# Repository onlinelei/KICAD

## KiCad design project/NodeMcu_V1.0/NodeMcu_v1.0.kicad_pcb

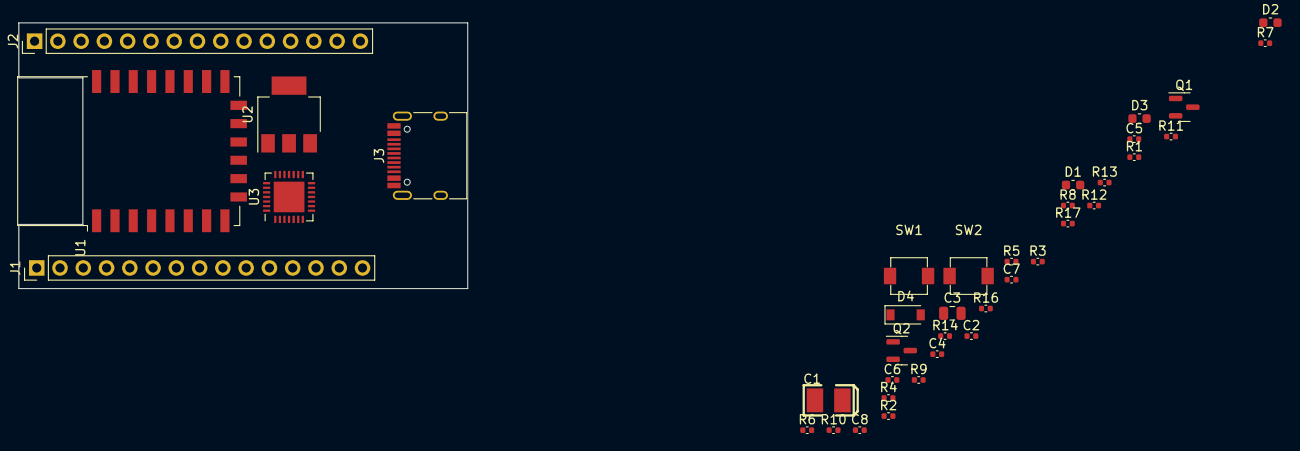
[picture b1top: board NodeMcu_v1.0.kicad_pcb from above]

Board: 2 copper layers, 49.0 x 29.0 mm, 38 parts (0 on the bottom side), 37 nets, no tracks yet.

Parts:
C1: 100uf; CASE-B_3528
C2, C6, C7: 100nf; C_0402_1005Metric
C3: 10uf 25v; C_0805_2012Metric
C4, C5, C8: 10uf; C_0402_1005Metric
D1: 3.3; C_0603_1608Metric
D2: TXD; C_0603_1608Metric
D3: RXD; C_0603_1608Metric
D4: B120-E3; D_SOD-123
J1: J2; PinHeader_1x15_P2.54mm_Vertical
J2: J1; PinHeader_1x15_P2.54mm_Vertical
J3: usbc; USB_C_Receptacle_HRO_TYPE-C-31-M-12
Q1: q1; SOT-23
Q2: q2; SOT-23
R1, R3, R10, R11, R12, R14: 12K; C_0402_1005Metric
R2, R8, R9, R13: 470; C_0402_1005Metric
R4, R5: 1k; C_0402_1005Metric
R6: 12k; C_0402_1005Metric
R7: 0; C_0402_1005Metric
R16: 220K(1%); C_0402_1005Metric
R17: 100K(1%); C_0402_1005Metric
SW1, SW2: SW_Push; SMD,3x4x2mm
U1: ESP-12E
U2: NCP1117-1.5_SOT223; SOT-223
U3: CP2102-GMR_[C6568]; QFN-28-1EP_5x5mm_P0.5mm_EP3.35x3.35mm

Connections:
+3V3: C1.1, C4.1, C5.1, C6.1, J1.11, J2.6, J2.15, R1.2, R2.1, R3.2, R4.1, R5.1, R6.2, R10.2, U1.8 (VCC), U2.2 (VO), U3.6 (VDD), U3.7 (REGIN)
+5VD: C3.1, D4.1 (K), U2.3 (VI)
/ADC: J1.2, R16.1, R17.1, U1.2 (ADC)
/ADC EX: J1.1, R16.2
/EN: J1.12, R6.1, U1.3 (EN)
/GPIO0: J2.4, Q2.3 (C), R1.1, R9.1, U1.18 (GPIO0)
/GPIO2: J2.5, R3.1, U1.17 (GPIO2)
/GPIO4: J2.3, U1.19 (GPIO4)
/GPIO5: J2.2, U1.20 (GPIO5)
/GPIO9: J1.5, U1.11 (GPIO9)
/GPIO10: J1.4, U1.12 (GPIO10)
/GPIO12: J2.9, U1.6 (GPIO12)
/GPIO13: J2.10, U1.7 (GPIO13)
/GPIO14: J2.8, U1.5 (GPIO14)
/GPIO15: J2.11, R11.1, U1.16 (GPIO15)
/GPIO16: D1.1 (K), J2.1, R7.1, U1.4 (GPIO16)
/RXD: D3.1 (K), J2.12, R13.1, U1.21 (GPIO3/RXD)
/SPI_CLK: J1.9, U1.14 (SCLK)
/SPI_INT: J1.6, U1.13 (MOSI)
/SPI_MISO: J1.8, U1.10 (MISO)
/SPI_MOSI: J1.7, U1.9 (CS0)
/TXD: D2.1 (K), J2.13, U1.22 (GPIO1/TXD), U3.25 (RXD)
/VDDUSB: C7.1, C8.1, D4.2 (A), J1.15, J3.A4 (VBUS), J3.A9 (VBUS), J3.B4 (VBUS), J3.B9 (VBUS), U3.8 (VBUS)
/nRST: C2.2, J1.13, Q1.3 (C), R8.1, R10.1, U1.1 (~RST)
GND: C1.2, C2.1, C3.2, C4.2, C5.2, C6.2, C7.2, C8.2, J1.10, J1.14, J2.7, J2.14, J3.A1 (GND), J3.A12 (GND), J3.B1 (GND), J3.B12 (GND), J3.S1 (SHIELD), R11.2, R17.2, SW1.2, SW2.2, U1.15 (GND), U2.1 (GND), U3.3 (GND)
unnamed: D1.2 (A), R2.2
unnamed: D2.2 (A), R4.2
unnamed: D3.2 (A), R5.2
unnamed: J3.A6 (D+), J3.B6 (D+), U3.4 (D+)
unnamed: J3.A7 (D-), J3.B7 (D-), U3.5 (D-)
unnamed: Q1.1 (B), R12.1
unnamed: Q1.2 (E), R14.2, U3.24 (RTS)
unnamed: Q2.1 (B), R14.1
unnamed: Q2.2 (E), R12.2, U3.28 (DTR)
unnamed: R7.2, R8.2, SW1.1
unnamed: R9.2, SW2.1
unnamed: R13.2, U3.26 (TXD)

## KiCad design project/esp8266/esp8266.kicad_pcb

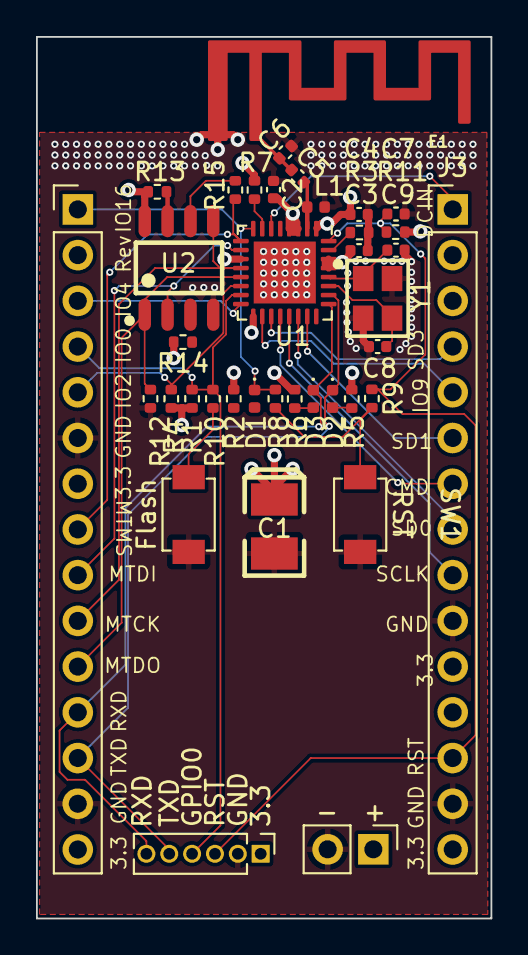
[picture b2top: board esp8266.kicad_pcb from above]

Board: 4 copper layers, 25.2 x 49.0 mm, 38 parts (0 on the bottom side), 34 nets.

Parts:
C1: 100uf; CASE-B_3528
C2: 1uF; C_0402_1005Metric
C3: 10uF; C_0402_1005Metric
C4: 0.1uF; C_0402_1005Metric
C5: 8.2pF; C_0402_1005Metric
C6: 2.4pF; C_0402_1005Metric
C7: 470pf; C_0402_1005Metric
C8, C9: 10pF; C_0402_1005Metric
D1: 3.3; LED_0402_1005Metric
D2: TXD; LED_0402_1005Metric
D3: RXD; LED_0402_1005Metric
E1: ANTENNA-GROUNDEDTRACE-15.2MM; RF_2.4GHZ_15.2MM
J1: power; PinHeader_1x02_P2.54mm_Vertical
J2: TTL; PinHeader_1x06_P1.27mm_Vertical
J3, J4: Conn_01x15_Female; PinHeader_1x15_P2.54mm_Vertical
L1: 1.5nH; L_0402_1005Metric
R1, R3, R4, R11, R12: 12K; R_0402_1005Metric
R2, R9, R10: 470; R_0402_1005Metric
R5, R6: 1k; R_0402_1005Metric
R7: 12k; R_0402_1005Metric
R8: 0; R_0402_1005Metric
R13, R14: 10K; R_0402_1005Metric
R15: 50; R_0402_1005Metric
SW1: RST; Button_SMD,3x4x2mm
SW2: Flash; Button_SMD,3x4x2mm
U1: ESP8266EX; QFN-32-1EP_5x5mm_P0.5mm_EP3.45x3.45mm
U2: Flash_SOP-8_150mil; SOP-8_150MIL
Y1: 26MHz; SMD-3225_4P

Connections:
+3V3: C1.1, C2.2, C3.2, C4.2, J1.1, J2.1, J3.11, J3.15, J4.7, J4.15, R1.2, R2.1, R4.2, R5.1, R6.1, R7.2, R11.2, R13.2, R14.2, U1.1 (VDDA), U1.3 (VDD3P3), U1.4 (VDD3P3), U1.11 (VDDPST), U1.17 (VDDPST), U1.29 (VDDD), U1.30 (VDDA), U2.8 (VCC)
/ADC_IN: J3.1, U1.6 (TOUT)
/CHIP_PU: R7.1, U1.7 (CHIP_PU)
/CMD/MOSI: J3.7, U1.20 (SDIO_CMD)
/GPIO0: J2.4, J4.4, R1.1, R10.1, U1.15 (GPIO0)
/GPIO2: J4.5, R4.1, U1.14 (GPIO2)
/GPIO4: J4.3, U1.16 (GPIO4)
/GPIO16: D1.1 (K), J4.1, R8.1, U1.8 (XPD_DCDC)
/MTCK: J4.10, U1.12 (MTCK), U2.5 (SI)
/MTDI: J4.9, U1.10 (MTDI), U2.2 (SO)
/MTDO: J4.11, R12.1, U1.13 (MTDO), U2.1 (CS)
/MTMS: J4.8, R15.2, U1.9 (MTMS)
/RST: C7.2, J2.3, J3.13, R9.1, R11.1, U1.32 (~EXT_RSTB)
/RXD: D3.1 (K), J2.6, J4.12, U1.25 (U0RXD)
/SCLK: J3.9, U1.21 (SDIO_CLK)
/SD0/MISO: J3.8, U1.22 (SDIO_DATA_0)
/SD1/INT: J3.6, U1.23 (SDIO_DATA_1)
/SD2/GPIO9: J3.5, U1.18 (SDIO_DATA_2)
/SD3/CS: J3.4, U1.19 (SDIO_DATA_3)
/TXD: D2.1 (K), J2.5, J4.13, U1.26 (U0TXD)
GND: C1.2, C2.1, C3.1, C4.1, C6.1, C7.1, C8.1, C9.1, E1.GND, J1.2, J2.2, J3.10, J3.14, J4.6, J4.14, L1.2, R3.1, R12.2, SW1.2, SW2.2, U1.33 (GND), U2.4 (GND), Y1.2, Y1.4
unnamed: C5.1, C6.2, E1.ANT (SIGNAL)
unnamed: C5.2, L1.1, U1.2 (LNA)
unnamed: C8.2, U1.27 (XTAL_OUT), Y1.3
unnamed: C9.2, U1.28 (XTAL_IN), Y1.1
unnamed: D1.2 (A), R2.2
unnamed: D2.2 (A), R5.2
unnamed: D3.2 (A), R6.2
unnamed: R3.2, U1.31 (RES12K)
unnamed: R8.2, R9.2, SW1.1
unnamed: R10.2, SW2.1
unnamed: R13.1, U2.7 (HOLD)
unnamed: R14.1, U2.3 (WP)
unnamed: R15.1, U2.6 (CLK)
